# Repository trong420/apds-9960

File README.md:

<div align="center">

<h1>Gesture Recognition With APDS-9960 Sensor</h1>
</div>

**Schematic** 

**PCB** 

**Gerber Viewer**

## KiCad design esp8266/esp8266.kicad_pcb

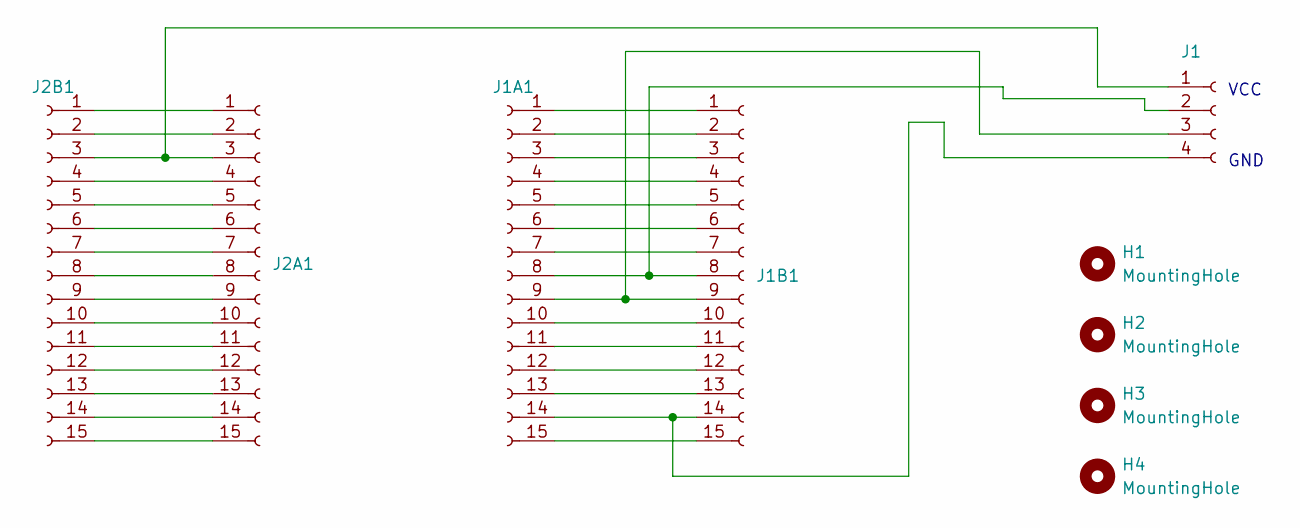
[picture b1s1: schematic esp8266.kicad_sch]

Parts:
H1, H2, H3, H4: MountingHole; MountingHole_3mm
J1: Conn_01x04_Female; PinSocket_1x04_P2.54mm_Vertical
J1A1, J1B1, J2A1, J2B1: Conn_01x15_Female; PinSocket_1x15_P2.54mm_Vertical

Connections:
unnamed: J1.1, J2A1.3, J2B1.3
unnamed: J1.2, J1A1.8, J1B1.8
unnamed: J1.3, J1A1.9, J1B1.9
unnamed: J1.4, J1A1.14, J1B1.14
unnamed: J1A1.1, J1B1.1
unnamed: J1A1.2, J1B1.2
unnamed: J1A1.3, J1B1.3
unnamed: J1A1.4, J1B1.4
unnamed: J1A1.5, J1B1.5
unnamed: J1A1.6, J1B1.6
unnamed: J1A1.7, J1B1.7
unnamed: J1A1.10, J1B1.10
unnamed: J1A1.11, J1B1.11
unnamed: J1A1.12, J1B1.12
unnamed: J1A1.13, J1B1.13
unnamed: J1A1.15, J1B1.15
unnamed: J2A1.1, J2B1.1
unnamed: J2A1.2, J2B1.2
unnamed: J2A1.4, J2B1.4
unnamed: J2A1.5, J2B1.5
unnamed: J2A1.6, J2B1.6
unnamed: J2A1.7, J2B1.7
unnamed: J2A1.8, J2B1.8
unnamed: J2A1.9, J2B1.9
unnamed: J2A1.10, J2B1.10
unnamed: J2A1.11, J2B1.11
unnamed: J2A1.12, J2B1.12
unnamed: J2A1.13, J2B1.13
unnamed: J2A1.14, J2B1.14
unnamed: J2A1.15, J2B1.15

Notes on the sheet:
GND
VCC

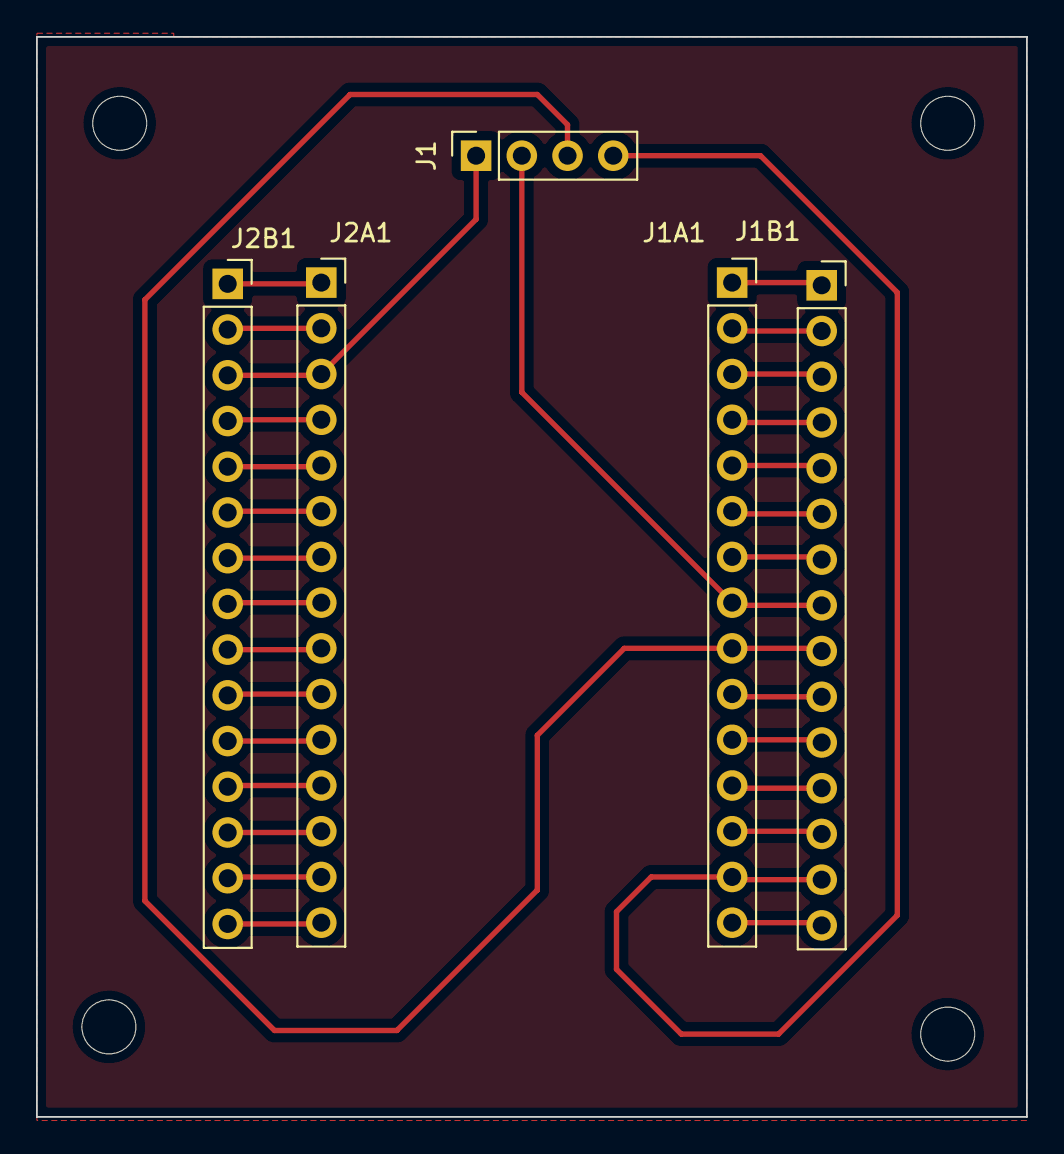
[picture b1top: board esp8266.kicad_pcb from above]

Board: 2 copper layers, 55.0 x 60.0 mm, 9 parts (0 on the bottom side), 30 nets.

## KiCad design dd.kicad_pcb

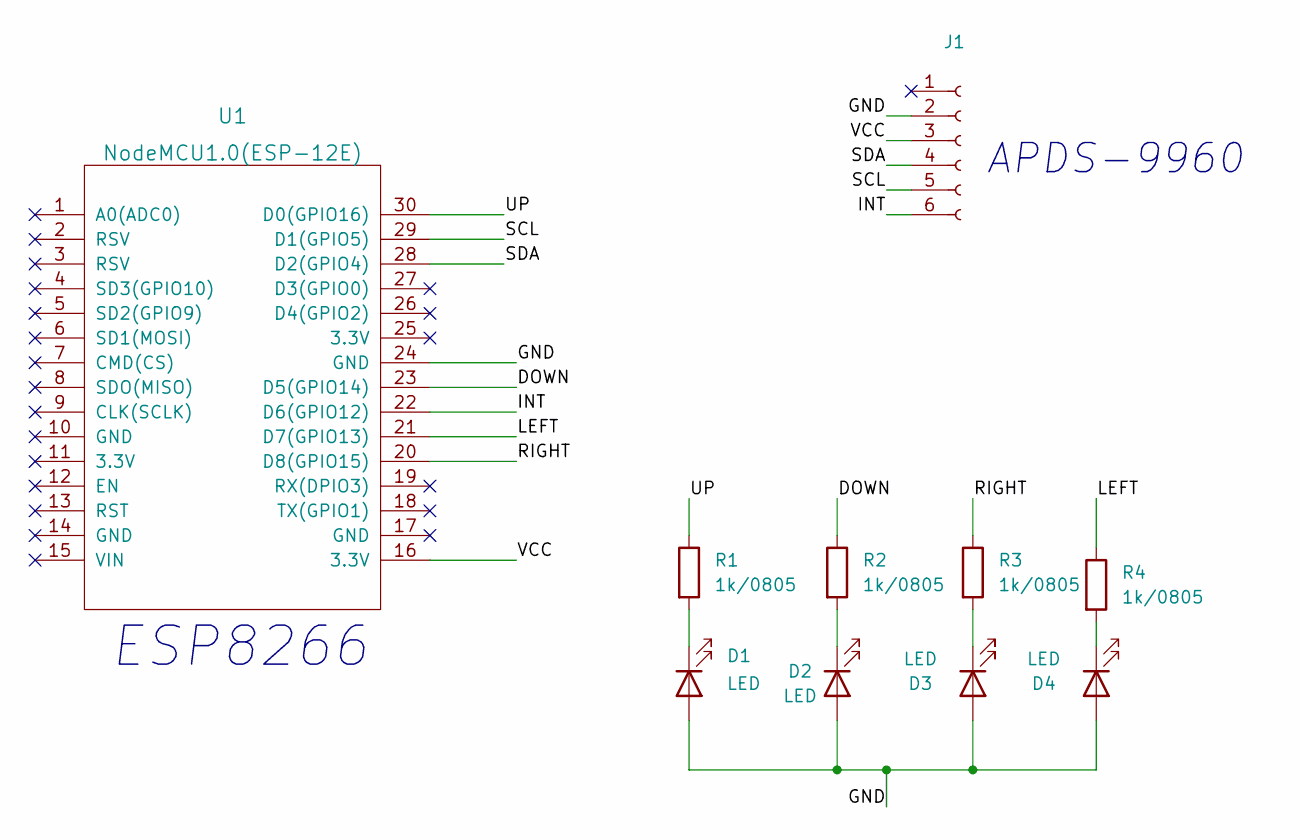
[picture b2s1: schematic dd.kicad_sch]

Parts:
D1, D2, D3, D4: LED; LED_0805_2012Metric_Pad1.15x1.40mm_HandSolder
J1: Conn_01x06_Female; PinSocket_1x06_P2.54mm_Vertical
R1, R2, R3, R4: 1k/0805; R_0805_2012Metric
U1: NodeMCU1.0(ESP-12E); NodeMCU-LoLinV3

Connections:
/DOWN: R2.1, U1.23 (D5(GPIO14))
/GND: D1.2 (A), D2.2 (A), D3.2 (A), D4.2 (A), J1.2, U1.24 (GND)
/INT: J1.6, U1.22 (D6(GPIO12))
/LEFT: R4.1, U1.21 (D7(GPIO13))
/RIGHT: R3.1, U1.20 (D8(GPIO15))
/SCL: J1.5, U1.29 (D1(GPIO5))
/SDA: J1.4, U1.28 (D2(GPIO4))
/UP: R1.1, U1.30 (D0(GPIO16))
/VCC: J1.3, U1.16 (3.3V)
unnamed: D1.1 (K), R1.2
unnamed: D2.1 (K), R2.2
unnamed: D3.1 (K), R3.2
unnamed: D4.1 (K), R4.2

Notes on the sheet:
ESP8266
APDS-9960

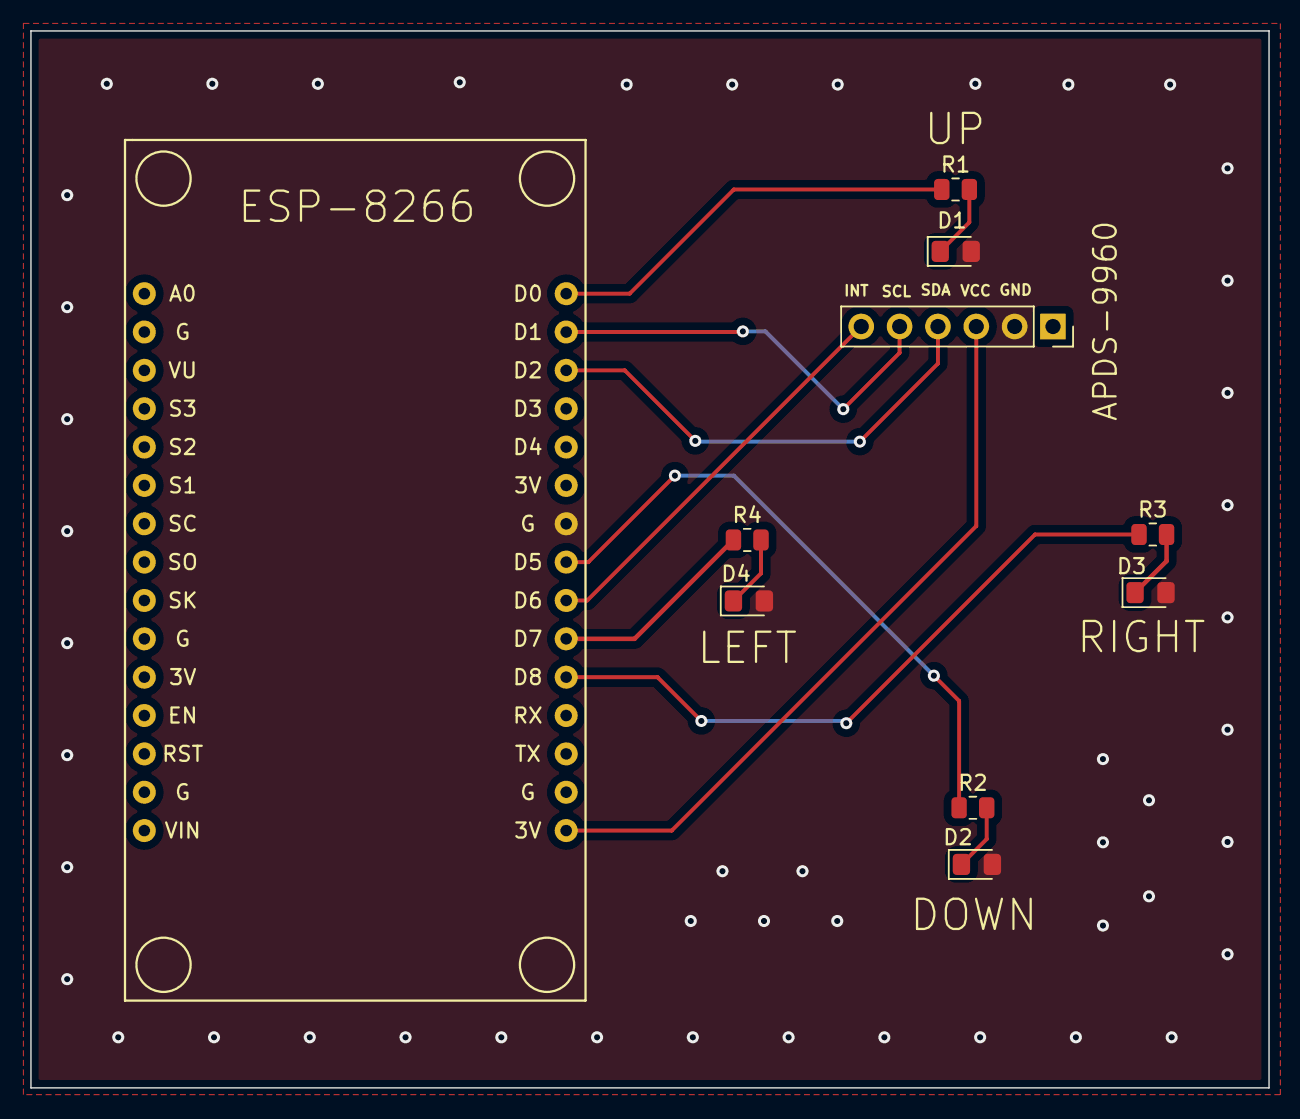
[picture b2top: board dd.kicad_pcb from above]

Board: 2 copper layers, 82.0 x 70.0 mm, 10 parts (0 on the bottom side), 13 nets.

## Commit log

2024-03-16 add gesture code
